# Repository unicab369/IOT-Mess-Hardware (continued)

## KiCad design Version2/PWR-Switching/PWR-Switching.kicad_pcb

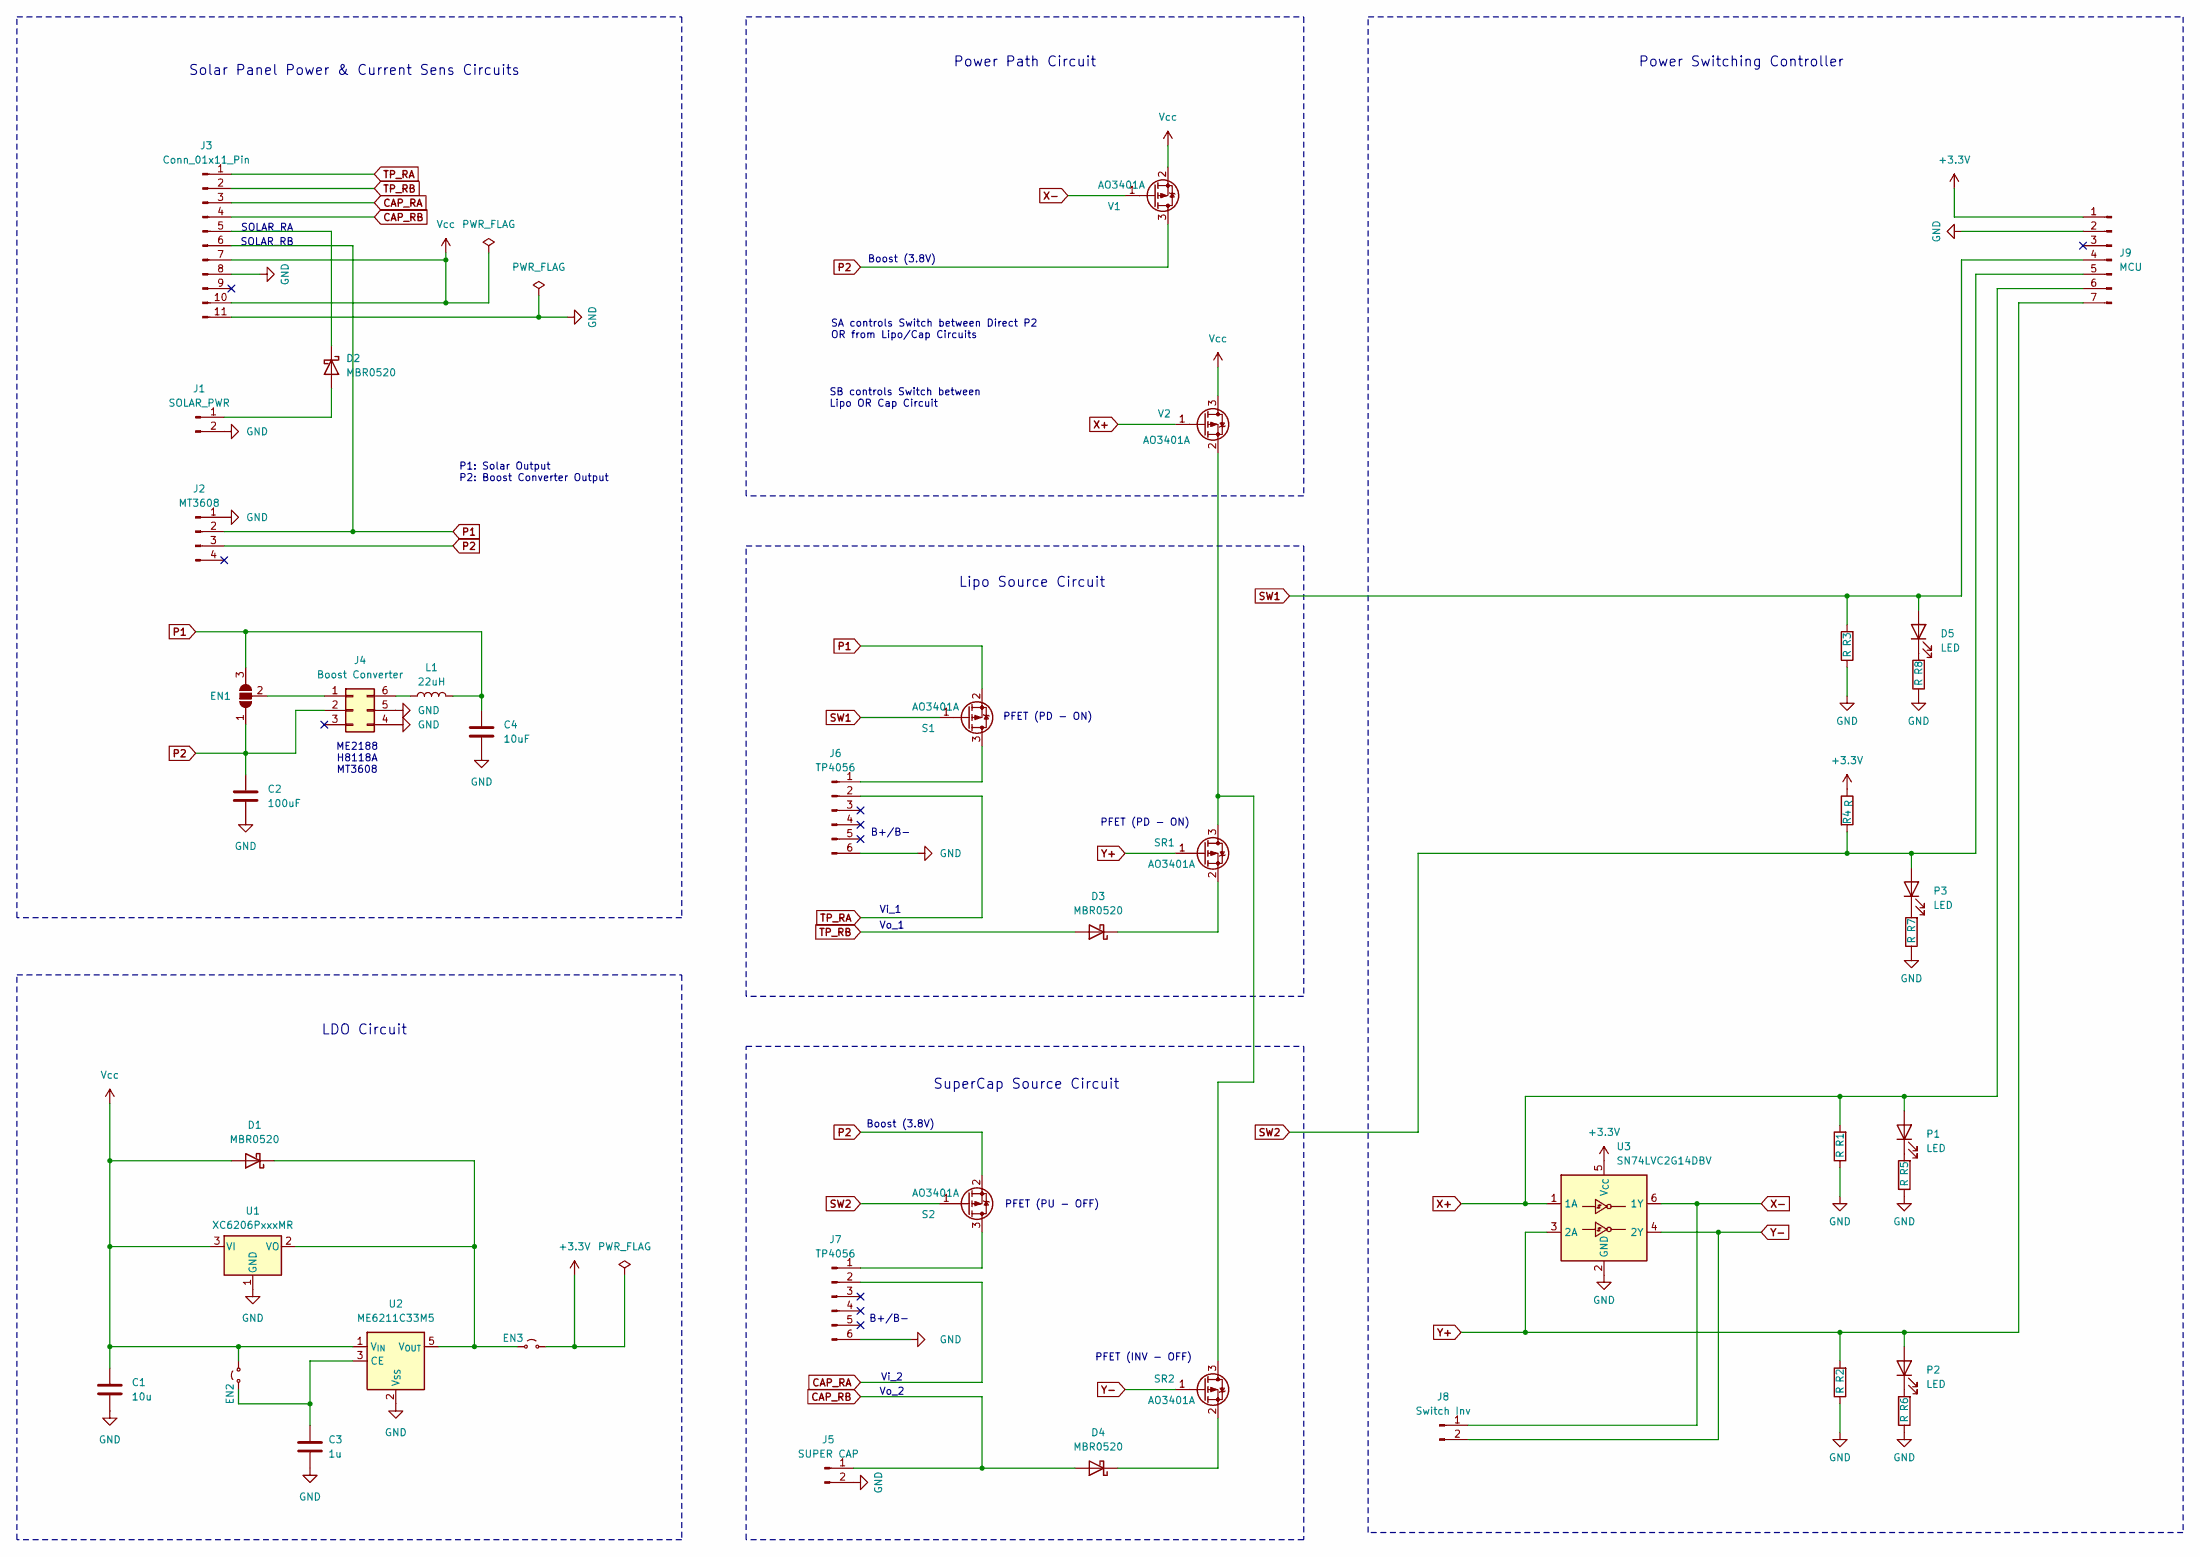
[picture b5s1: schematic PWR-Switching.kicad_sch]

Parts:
C1: 10u; C_0603_1608Metric
C2: 100uF; C_0603_1608Metric
C3: 1u; C_0603_1608Metric
C4: 10uF; C_0603_1608Metric
D1, D2, D3, D4: MBR0520; D_SOD-123
D5: LED; LED_0603_1608Metric
EN1: Jumper; Jumper-3_P1.3mm_Open_RoundedPad1.0x1.5mm
EN2, EN3: Jumper_2; Jumpper-triangle
J1: SOLAR_PWR; PinHeader_1x02_P2.54mm_Vertical
J2: MT3608; PinHeader_1x04_P2.54mm_Vertical
J3: Conn_01x11_Pin; PinHeader_1x11_P2.54mm_Vertical
J4: Boost Converter; SOT-23-6
J5: SUPER CAP; PinHeader_1x02_P2.54mm_Vertical
J6, J7: TP4056; PinHeader_1x06_P2.54mm_Vertical
J8: Switch Inv; PinSocket_1x02_P1.00mm_Vertical
J9: MCU; PinHeader_1x07_P2.54mm_Vertical
L1: 22uH; Inductor_4x4_5x5mm
P1, P2, P3: LED; LED_0603_1608Metric
R1, R2, R3, R4, R5, R6, R7, R8: R; R_0603_1608Metric
S1, S2: AO3401A; SOT-23
SR1, SR2: AO3401A; SOT-23
U1: XC6206PxxxMR; SOT-23-3
U2: ME6211C33M5; SOT-23-5
U3: SN74LVC2G14DBV; SOT-23-6
V1, V2: AO3401A; SOT-23

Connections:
+3.3V: EN3.2 (B), J9.1, R4.1, U3.5 (V_{CC})
CAP_RA: J3.3, J7.2
CAP_RB: D4.2 (A), J3.4, J5.1
GND: C1.2, C2.2, C3.2, C4.2, J1.2, J2.1, J3.8, J3.11, J4.4, J4.5, J5.2, J6.6, J7.6, J9.2, R1.1, R2.1, R3.1, R5.1, R6.1, R7.1, R8.1, U1.1 (GND), U2.2 (V_{SS}), U3.2 (GND)
unnamed: D1.1 (K), EN3.1 (A), U1.2 (VO), U2.5 (V_{OUT})
unnamed: D2.2 (A), J1.1
unnamed: D2.1 (K), J3.5
unnamed: D3.1 (K), SR1.2 (S)
unnamed: D4.1 (K), SR2.2 (S)
unnamed: D5.1 (K), R8.2
unnamed: EN1.2 (C), J4.1
unnamed: C3.1, EN2.1 (A), U2.3 (CE)
unnamed: J4.6, L1.1
unnamed: J6.1, S1.3 (D)
unnamed: J7.1, S2.3 (D)
unnamed: P1.1 (K), R5.2
unnamed: P2.1 (K), R6.2
unnamed: P3.1 (K), R7.2
unnamed: SR1.3 (D), SR2.3 (D), V2.2 (S)
P1: C4.1, EN1.3 (B), J2.2, J3.6, L1.2, S1.2 (S)
P2: C2.1, EN1.1 (A), J2.3, J4.2, S2.2 (S), V1.3 (D)
SW1: D5.2 (A), J9.4, R3.2, S1.1 (G)
SW2: J9.5, P3.2 (A), R4.2, S2.1 (G)
TP_RA: J3.1, J6.2
TP_RB: D3.2 (A), J3.2
Vcc: C1.1, D1.2 (A), EN2.2 (B), J3.7, J3.10, U1.3 (VI), U2.1 (V_{IN}), V1.2 (S), V2.3 (D)
X+: J9.6, P1.2 (A), R1.2, U3.1 (1A), V2.1 (G)
X-: J8.1, U3.6 (1Y), V1.1 (G)
Y+: J9.7, P2.2 (A), R2.2, SR1.1 (G), U3.3 (2A)
Y-: J8.2, SR2.1 (G), U3.4 (2Y)

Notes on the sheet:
Solar Panel Power & Current Sens Circuits
PFET (PD - ON)
Boost (3.8V)
SA controls Switch between Direct P2 OR from Lipo/Cap Circuits
SuperCap Source Circuit
Vi_2
LDO Circuit
PFET (INV - OFF)
Power Path Circuit
ME2188 H8118A MT3608
Power Switching Controller
Vo_2
SOLAR_RB
B+/B-
Vo_1
P1: Solar Output P2: Boost Converter Output
SB controls Switch between Lipo OR Cap Circuit
SOLAR_RA
PFET (PU - OFF)
Lipo Source Circuit
Vi_1

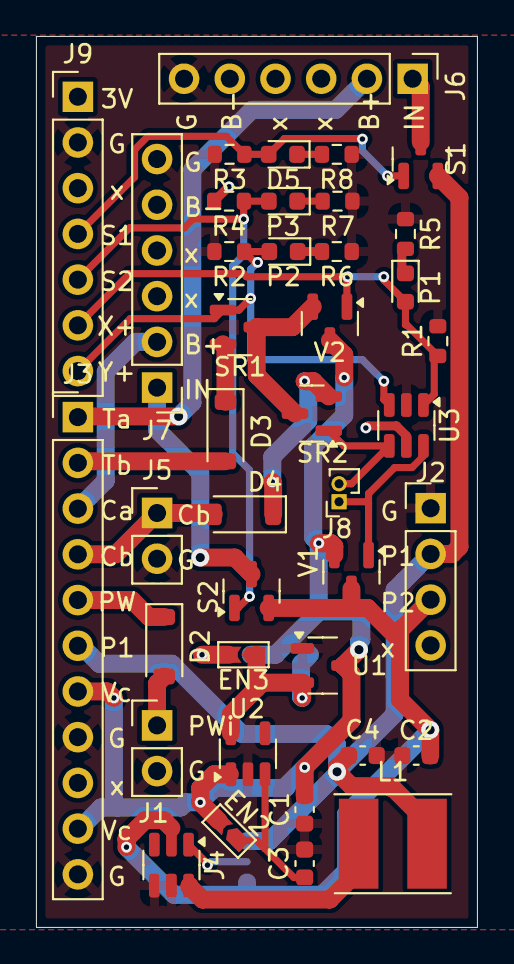
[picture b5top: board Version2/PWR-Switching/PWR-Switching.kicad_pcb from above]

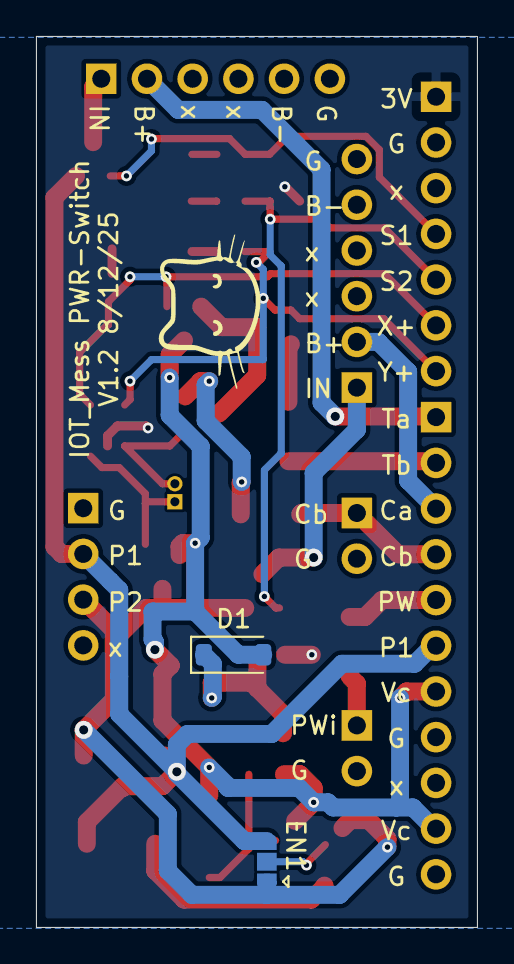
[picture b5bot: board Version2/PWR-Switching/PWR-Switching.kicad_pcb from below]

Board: 2 copper layers, 24.5 x 49.5 mm, 42 parts (2 on the bottom side), 30 nets.

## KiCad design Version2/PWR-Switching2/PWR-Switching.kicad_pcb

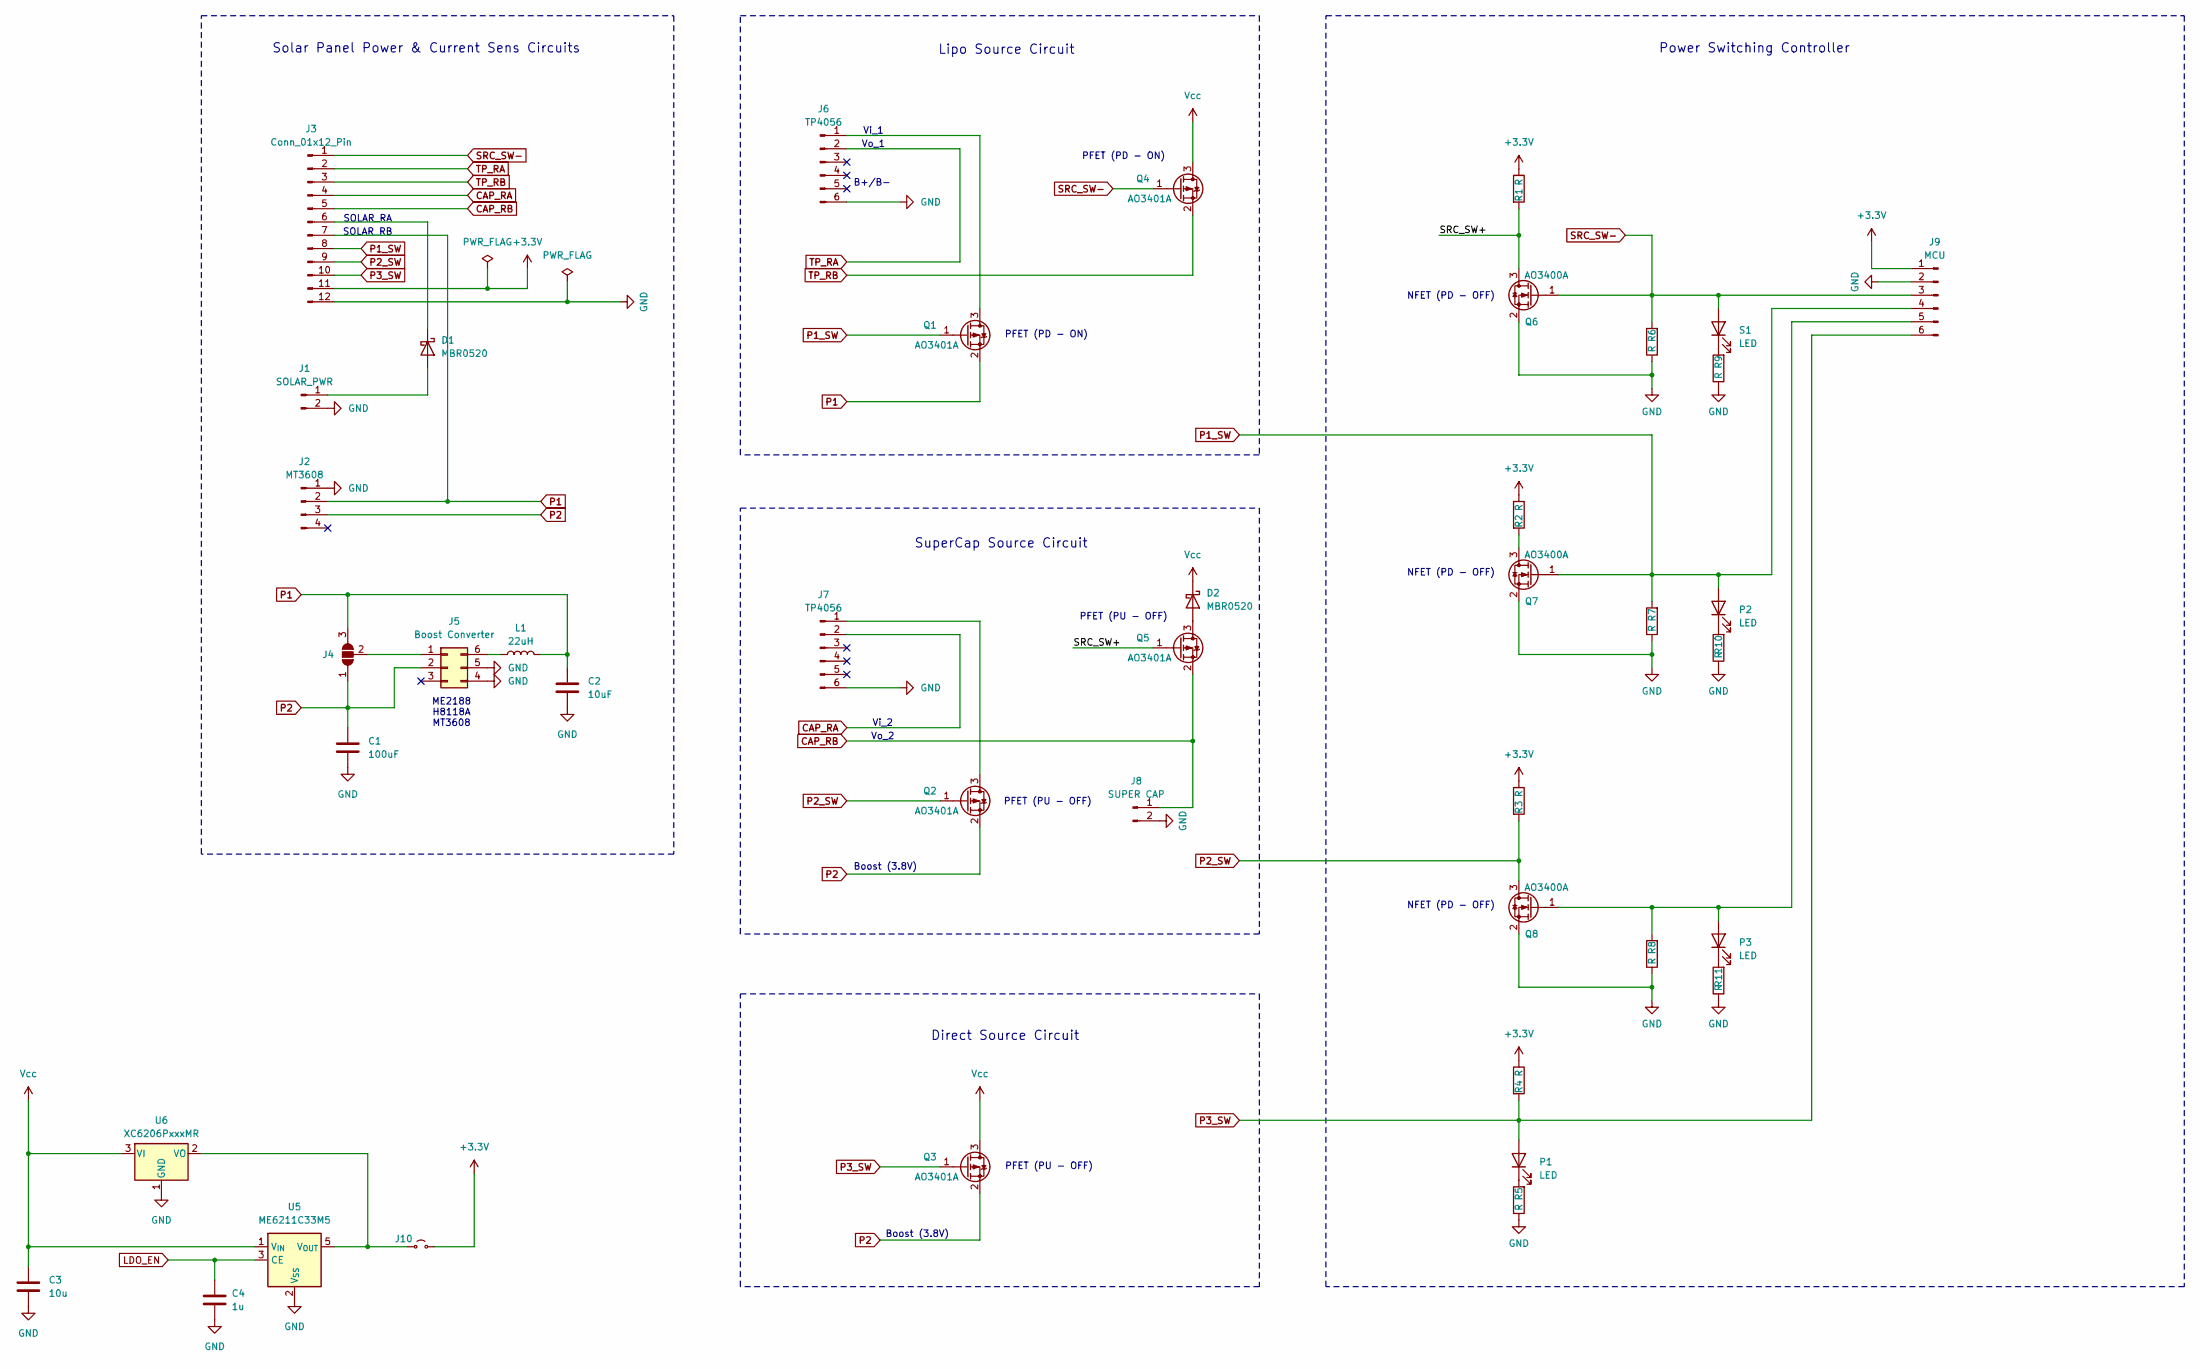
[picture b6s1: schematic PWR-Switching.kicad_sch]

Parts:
C1: 100uF; C_0603_1608Metric
C2: 10uF; C_0603_1608Metric
C3: 10u; C_0603_1608Metric
C4: 1u; C_0603_1608Metric
D1, D2: MBR0520; D_SOD-123
J1: SOLAR_PWR; PinHeader_1x02_P2.54mm_Vertical
J2: MT3608; PinHeader_1x04_P2.54mm_Vertical
J3: Conn_01x12_Pin; PinHeader_1x12_P2.54mm_Vertical
J4: Jumper; Jumper-3_P1.3mm_Open_RoundedPad1.0x1.5mm
J5: Boost Converter; SOT-23-6
J6, J7: TP4056; PinHeader_1x06_P2.54mm_Vertical
J8: SUPER CAP; PinHeader_1x02_P2.54mm_Vertical
J9: MCU; PinHeader_1x06_P2.54mm_Vertical
J10: Jumper_2; Jumpper-triangle
L1: 22uH; Inductor_4x4_5x5mm
P1, P2, P3: LED; LED_0603_1608Metric
Q1, Q2, Q3, Q4, Q5: AO3401A; SOT-23
Q6, Q7, Q8: AO3400A; SOT-23
R1, R2, R3, R4, R5, R6, R7, R8, R9, R10, R11: R; R_0603_1608Metric
S1: LED; LED_0603_1608Metric
U5: ME6211C33M5; SOT-23-5
U6: XC6206PxxxMR; SOT-23-3

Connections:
+3.3V: J3.11, J9.1, J10.2 (B), R1.1, R2.1, R3.1, R4.1
/SRC_SW+: Q5.1 (G), Q6.3 (D), R1.2
CAP_RA: J3.4, J7.2
CAP_RB: J3.5, J8.1, Q5.2 (S)
GND: C1.2, C2.2, C3.2, C4.2, J1.2, J2.1, J3.12, J5.4, J5.5, J6.6, J7.6, J8.2, J9.2, Q6.2 (S), Q7.2 (S), Q8.2 (S), R5.1, R6.1, R7.1, R8.1, R9.1, R10.1, R11.1, U5.2 (V_{SS}), U6.1 (GND)
LDO_EN: C4.1, U5.3 (CE)
unnamed: D1.2 (A), J1.1
unnamed: D1.1 (K), J3.6
unnamed: D2.2 (A), Q5.3 (D)
unnamed: J4.2 (C), J5.1
unnamed: J5.6, L1.1
unnamed: J6.1, Q1.3 (D)
unnamed: J7.1, Q2.3 (D)
unnamed: J9.5, P3.2 (A), Q8.1 (G), R8.2
unnamed: J10.1 (A), U5.5 (V_{OUT}), U6.2 (VO)
unnamed: P1.1 (K), R5.2
unnamed: P2.1 (K), R10.2
unnamed: P3.1 (K), R11.2
unnamed: Q7.3 (D), R2.2
unnamed: R9.2, S1.1 (K)
P1: C2.1, J2.2, J3.7, J4.3 (B), L1.2, Q1.2 (S)
P1_SW: J3.8, J9.4, P2.2 (A), Q1.1 (G), Q7.1 (G), R7.2
P2: C1.1, J2.3, J4.1 (A), J5.2, Q2.2 (S), Q3.2 (S)
P2_SW: J3.9, Q2.1 (G), Q8.3 (D), R3.2
P3_SW: J3.10, J9.6, P1.2 (A), Q3.1 (G), R4.2
SRC_SW-: J3.1, J9.3, Q4.1 (G), Q6.1 (G), R6.2, S1.2 (A)
TP_RA: J3.2, J6.2
TP_RB: J3.3, Q4.2 (S)
Vcc: C3.1, D2.1 (K), Q3.3 (D), Q4.3 (D), U5.1 (V_{IN}), U6.3 (VI)

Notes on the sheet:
Solar Panel Power & Current Sens Circuits
PFET (PD - ON)
Boost (3.8V)
SuperCap Source Circuit
Vi_2
PFET (PU - OFF)
Direct Source Circuit
NFET (PD - OFF)
ME2188 H8118A MT3608
Power Switching Controller
Vo_2
SOLAR_RB
Vo_1
SOLAR_RA
B+/B-
Lipo Source Circuit
Vi_1

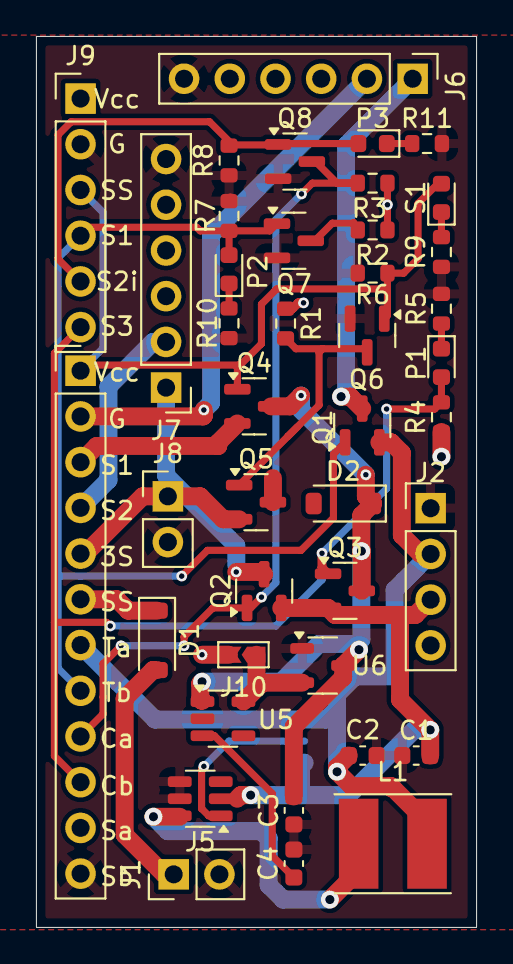
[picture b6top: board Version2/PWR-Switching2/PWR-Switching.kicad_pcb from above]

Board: 2 copper layers, 24.5 x 49.5 mm, 42 parts (1 on the bottom side), 29 nets.

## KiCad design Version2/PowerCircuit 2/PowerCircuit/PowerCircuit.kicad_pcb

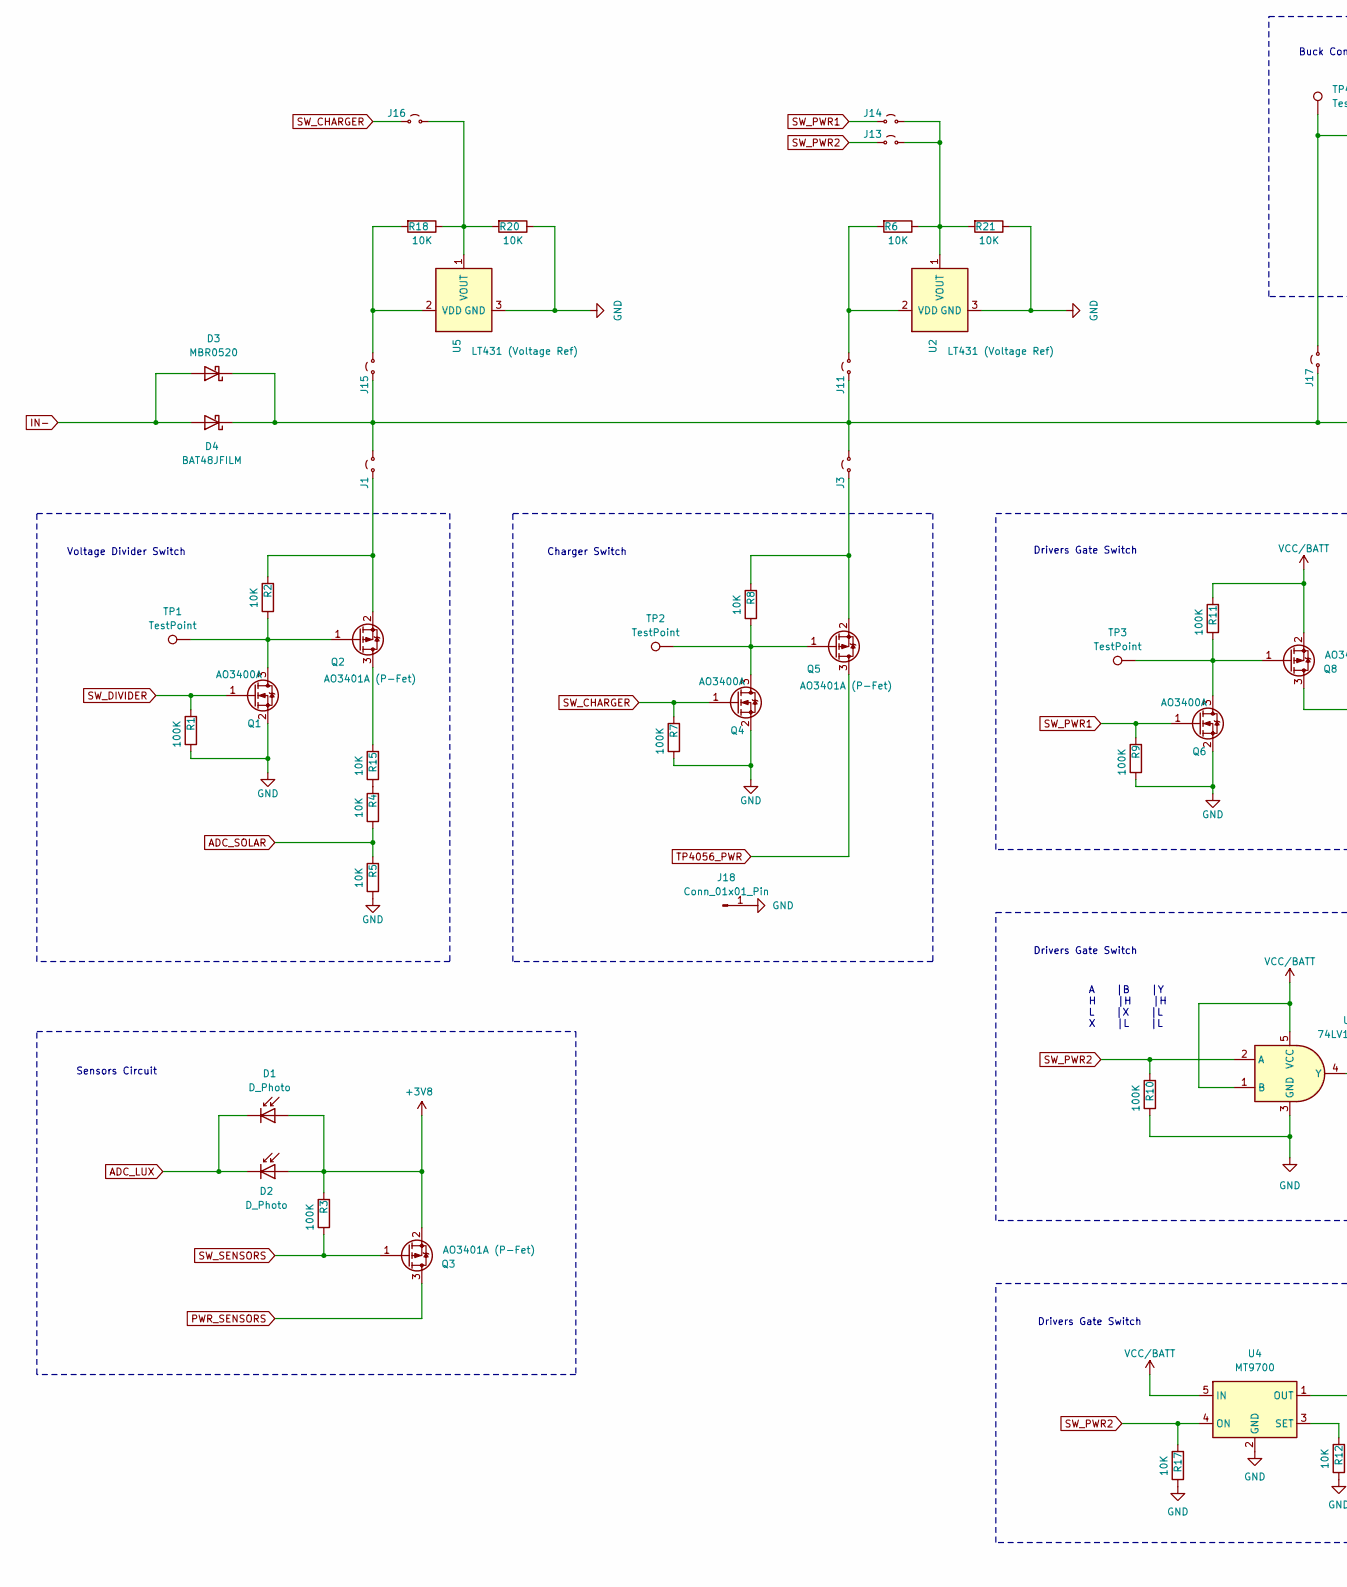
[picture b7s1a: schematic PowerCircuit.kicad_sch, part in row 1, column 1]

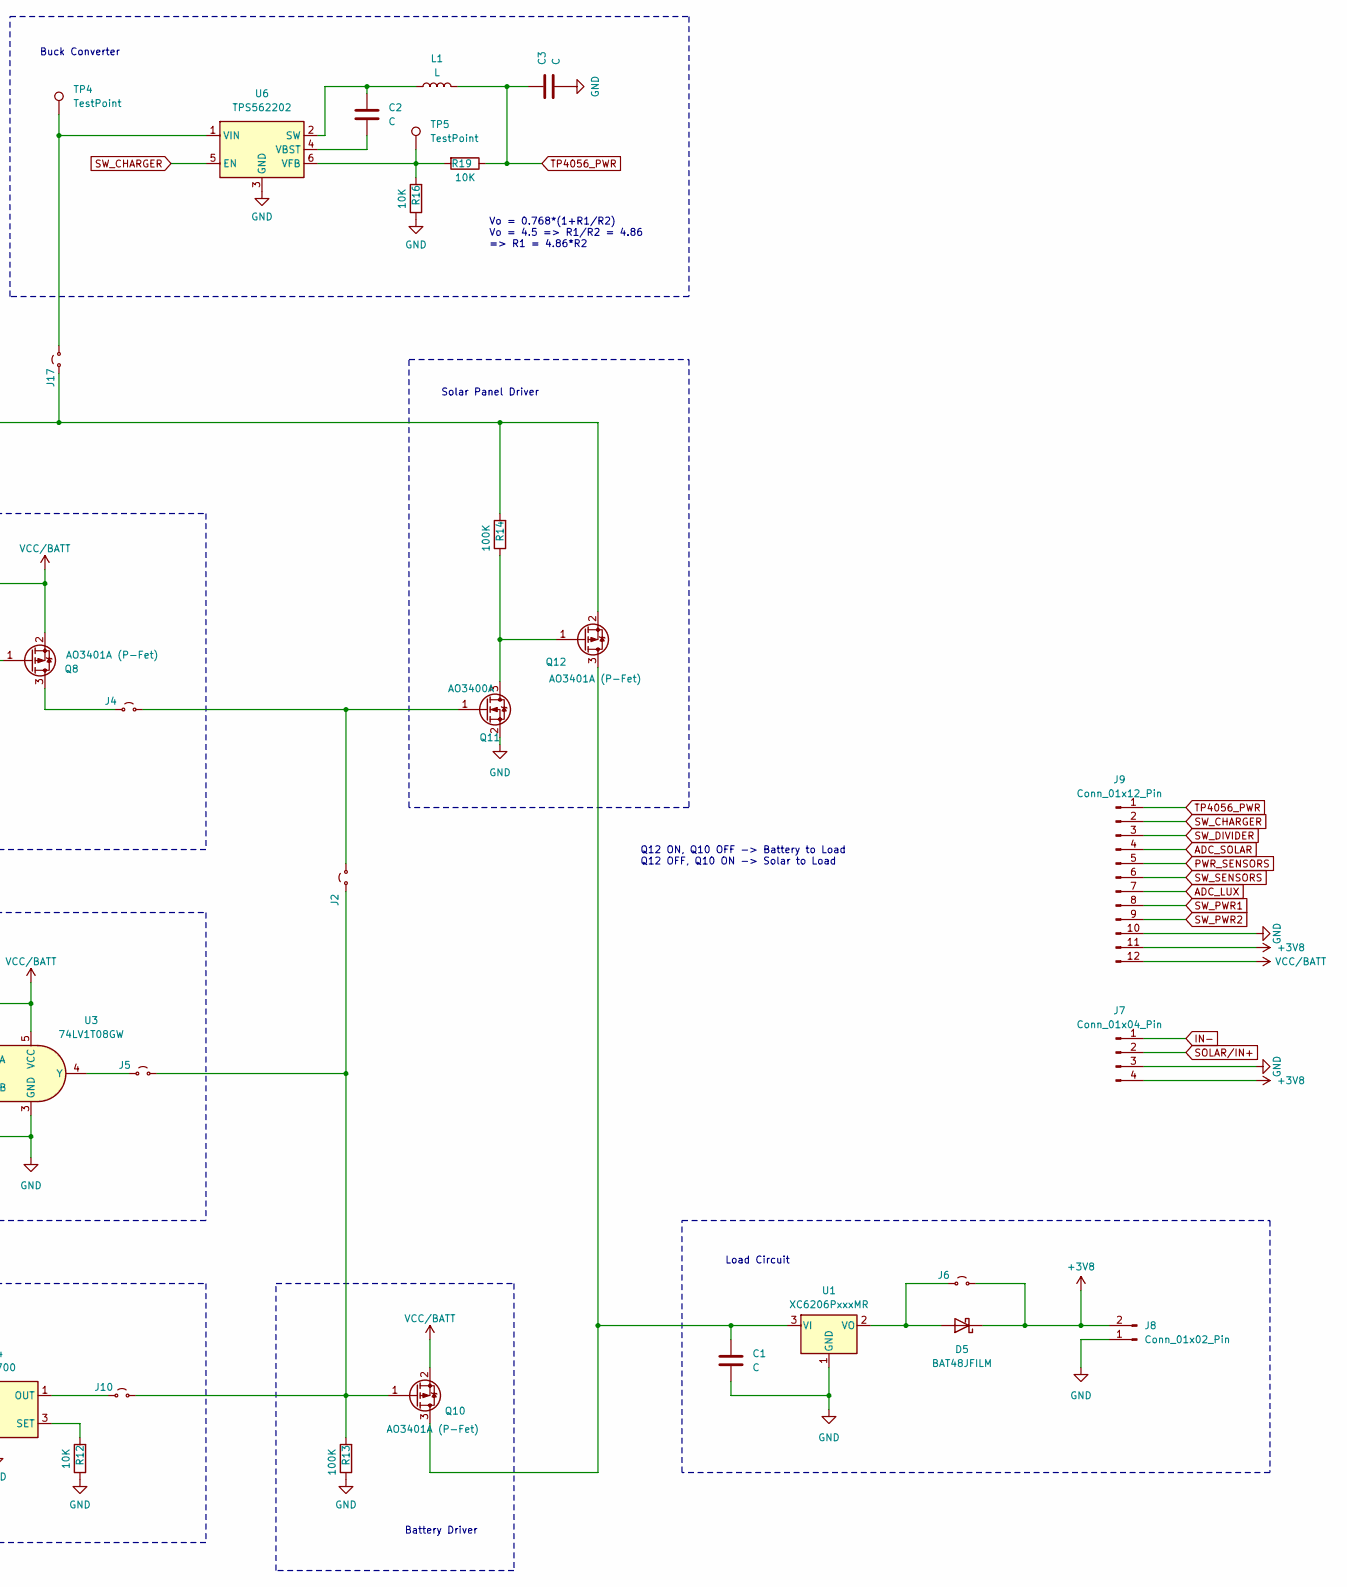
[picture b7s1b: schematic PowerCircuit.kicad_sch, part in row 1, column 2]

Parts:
C1, C2, C3: C; C_0603_1608Metric
D1: D_Photo; LED_0603_1608Metric
D2: D_Photo; LED_0805_2012Metric
D3: MBR0520; D_SOD-123
D4, D5: BAT48JFILM; D_SOD-323
J1, J2, J3, J4, J5, J6, J10, J11, J13, J14, J15, J16, J17: Jumper_2; Jumpper-triangle
J7: Conn_01x04_Pin; PinHeader_1x04_P2.54mm_Vertical
J8: Conn_01x02_Pin; PinHeader_1x02_P1.00mm_Vertical
J9: Conn_01x12_Pin; PinHeader_1x12_P2.54mm_Vertical
J18: Conn_01x01_Pin; PinHeader_1x01_P2.54mm_Vertical
L1: L; L_Neosid_SMS-ME3010
Q1, Q4, Q6, Q11: AO3400A; SOT-23
Q2, Q3, Q5, Q8, Q10, Q12: AO3401A (P-Fet); SOT-23
R1, R3, R7, R9, R10, R11, R13, R14: 100K; R_0805_2012Metric
R2, R4, R5, R6, R8, R12, R15, R16, R17, R18, R19, R20, R21: 10K; R_0805_2012Metric
TP1, TP2, TP3, TP4, TP5: TestPoint; PinHeader_1x01_P1.00mm_Vertical
U1: XC6206PxxxMR; SOT-23-3
U2, U5: LT431 (Voltage Ref); SOT-23
U3: 74LV1T08GW; SOT-353_SC-70-5
U4: MT9700; SOT-23-5
U6: TPS562202; SOT-563

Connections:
+3V8: D1.2 (A), D2.2 (A), D5.1 (K), J6.2 (B), J7.4, J8.2, J9.11, Q3.2 (S), R3.2
ADC_LUX: D1.1 (K), D2.1 (K), J9.7
ADC_SOLAR: J9.4, R4.1, R5.2
GND: C1.2, C3.1, J7.3, J8.1, J9.10, J18.1, Q1.2 (S), Q4.2 (S), Q6.2 (S), Q11.2 (S), R1.1, R5.1, R7.1, R9.1, R10.1, R12.1, R13.1, R16.1, R17.1, R20.1, R21.1, U1.1 (GND), U2.3 (GND), U3.3 (GND), U4.2 (GND), U5.3 (GND), U6.3 (GND)
IN-: D3.2 (A), D4.2 (A), J7.1
unnamed: D3.1 (K), D4.1 (K), J1.2 (B), J3.2 (B), J11.1 (A), J15.1 (A), J17.1 (A), Q12.2 (S), R14.2
unnamed: D5.2 (A), J6.1 (A), U1.2 (VO)
unnamed: J1.1 (A), Q2.2 (S), R2.2
unnamed: J2.2 (B), J4.2 (B), Q11.1 (G)
unnamed: J3.1 (A), Q5.2 (S), R8.2
unnamed: J4.1 (A), Q8.3 (D)
unnamed: J5.1 (A), U3.4 (Y)
unnamed: J10.1 (A), U4.1 (OUT)
unnamed: J2.1 (A), J5.2 (B), J10.2 (B), Q10.1 (G), R13.2
unnamed: J11.2 (B), R6.2, U2.2 (VDD)
unnamed: J13.2 (B), J14.2 (B), R6.1, R21.2, U2.1 (VOUT)
unnamed: J15.2 (B), R18.2, U5.2 (VDD)
unnamed: J16.2 (B), R18.1, R20.2, U5.1 (VOUT)
unnamed: J17.2 (B), TP4.1, U6.1 (VIN)
unnamed: Q1.3 (D), Q2.1 (G), R2.1, TP1.1
unnamed: Q2.3 (D), R15.2
unnamed: Q4.3 (D), Q5.1 (G), R8.1, TP2.1
unnamed: Q6.3 (D), Q8.1 (G), R11.1, TP3.1
unnamed: C1.1, Q10.3 (D), Q12.3 (D), U1.3 (VI)
unnamed: Q11.3 (D), Q12.1 (G), R14.1
unnamed: R4.2, R15.1
unnamed: R12.2, U4.3 (SET)
unnamed: C2.2, L1.1, U6.2 (SW)
unnamed: C2.1, U6.4 (VBST)
unnamed: R16.2, R19.2, TP5.1, U6.6 (VFB)
PWR_SENSORS: J9.5, Q3.3 (D)
SOLAR/IN+: J7.2
SW_CHARGER: J9.2, J16.1 (A), Q4.1 (G), R7.2, U6.5 (EN)
SW_DIVIDER: J9.3, Q1.1 (G), R1.2
SW_PWR1: J9.8, J14.1 (A), Q6.1 (G), R9.2
SW_PWR2: J9.9, J13.1 (A), R10.2, R17.2, U3.2 (A), U4.4 (ON)
SW_SENSORS: J9.6, Q3.1 (G), R3.1
TP4056_PWR: C3.2, J9.1, L1.2, Q5.3 (D), R19.1
VCC/BATT: J9.12, Q8.2 (S), Q10.2 (S), R11.2, U3.1 (B), U3.5 (VCC), U4.5 (IN)

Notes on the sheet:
Drivers Gate Switch
Solar Panel Driver
A |B |Y H |H |H L |X |L X |L |L
Voltage Divider Switch
Buck Converter
Load Circuit
Sensors Circuit
Q12 ON, Q10 OFF -> Battery to Load Q12 OFF, Q10 ON -> Solar to Load
Charger Switch
Battery Driver
Vo = 0.768*(1+R1/R2) Vo = 4.5 => R1/R2 = 4.86 => R1 = 4.86*R2

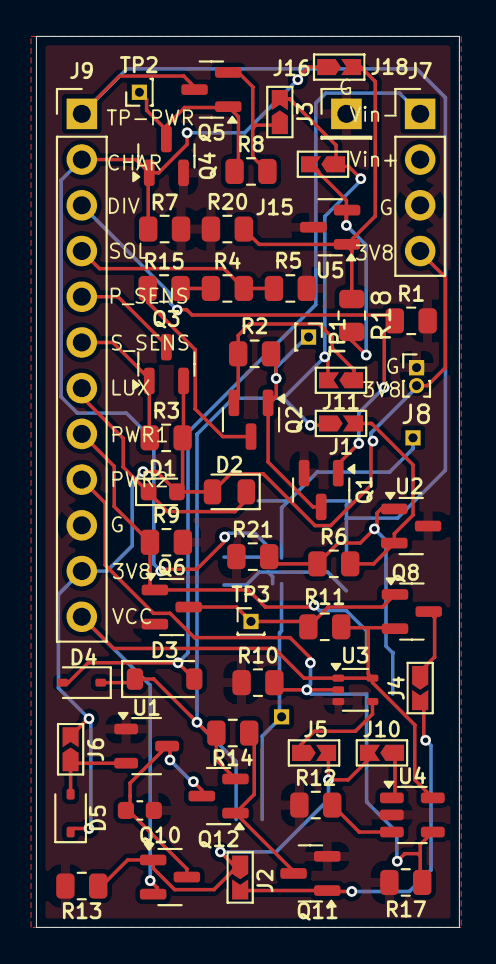
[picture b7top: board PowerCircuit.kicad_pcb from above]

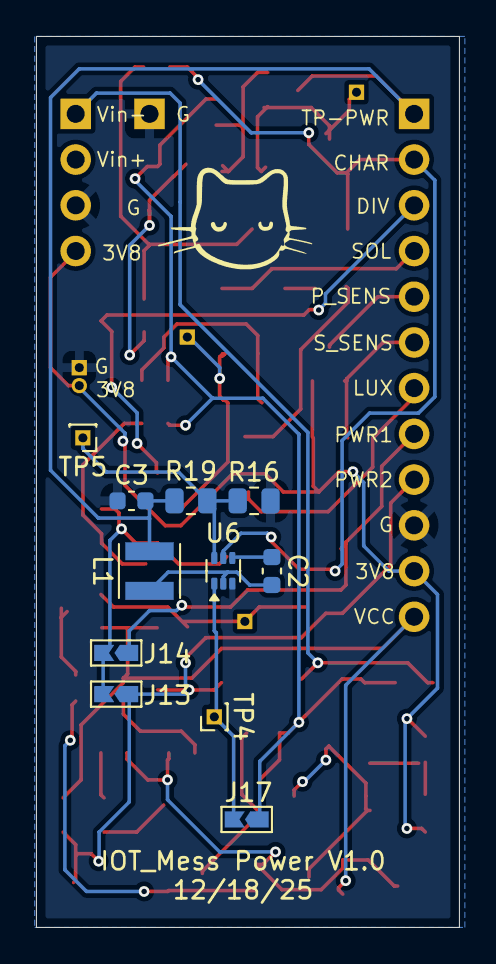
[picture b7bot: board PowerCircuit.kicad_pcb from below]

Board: 2 copper layers, 23.5 x 49.5 mm, 68 parts (11 on the bottom side), 38 nets.
